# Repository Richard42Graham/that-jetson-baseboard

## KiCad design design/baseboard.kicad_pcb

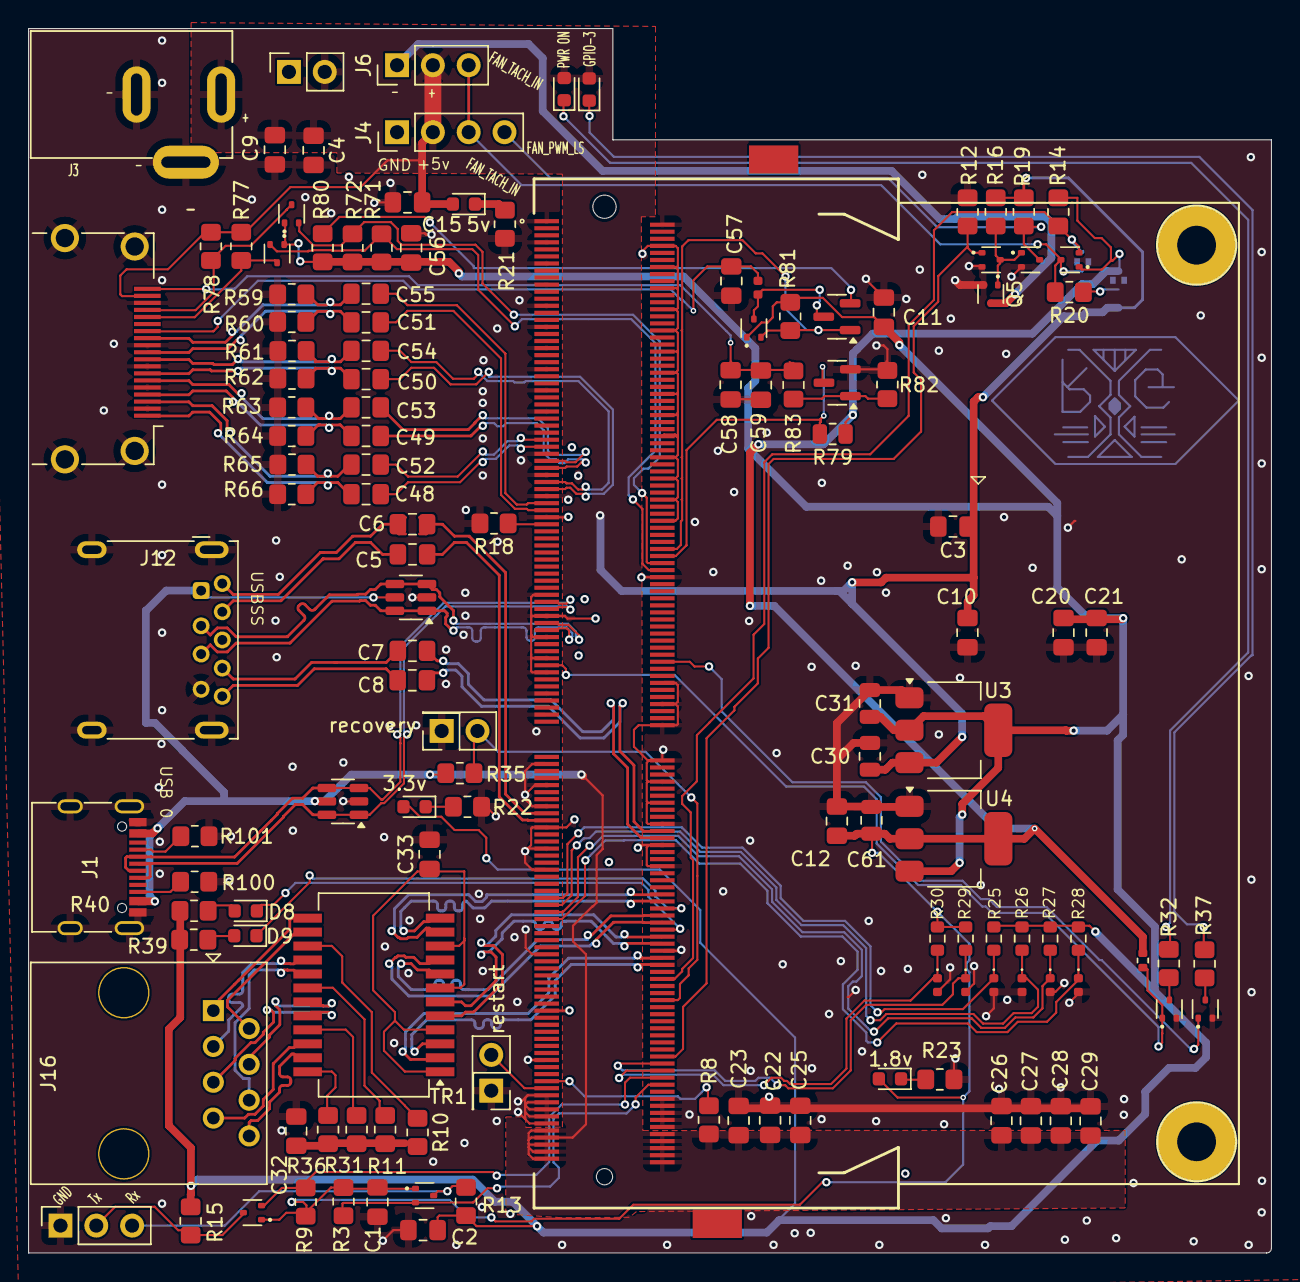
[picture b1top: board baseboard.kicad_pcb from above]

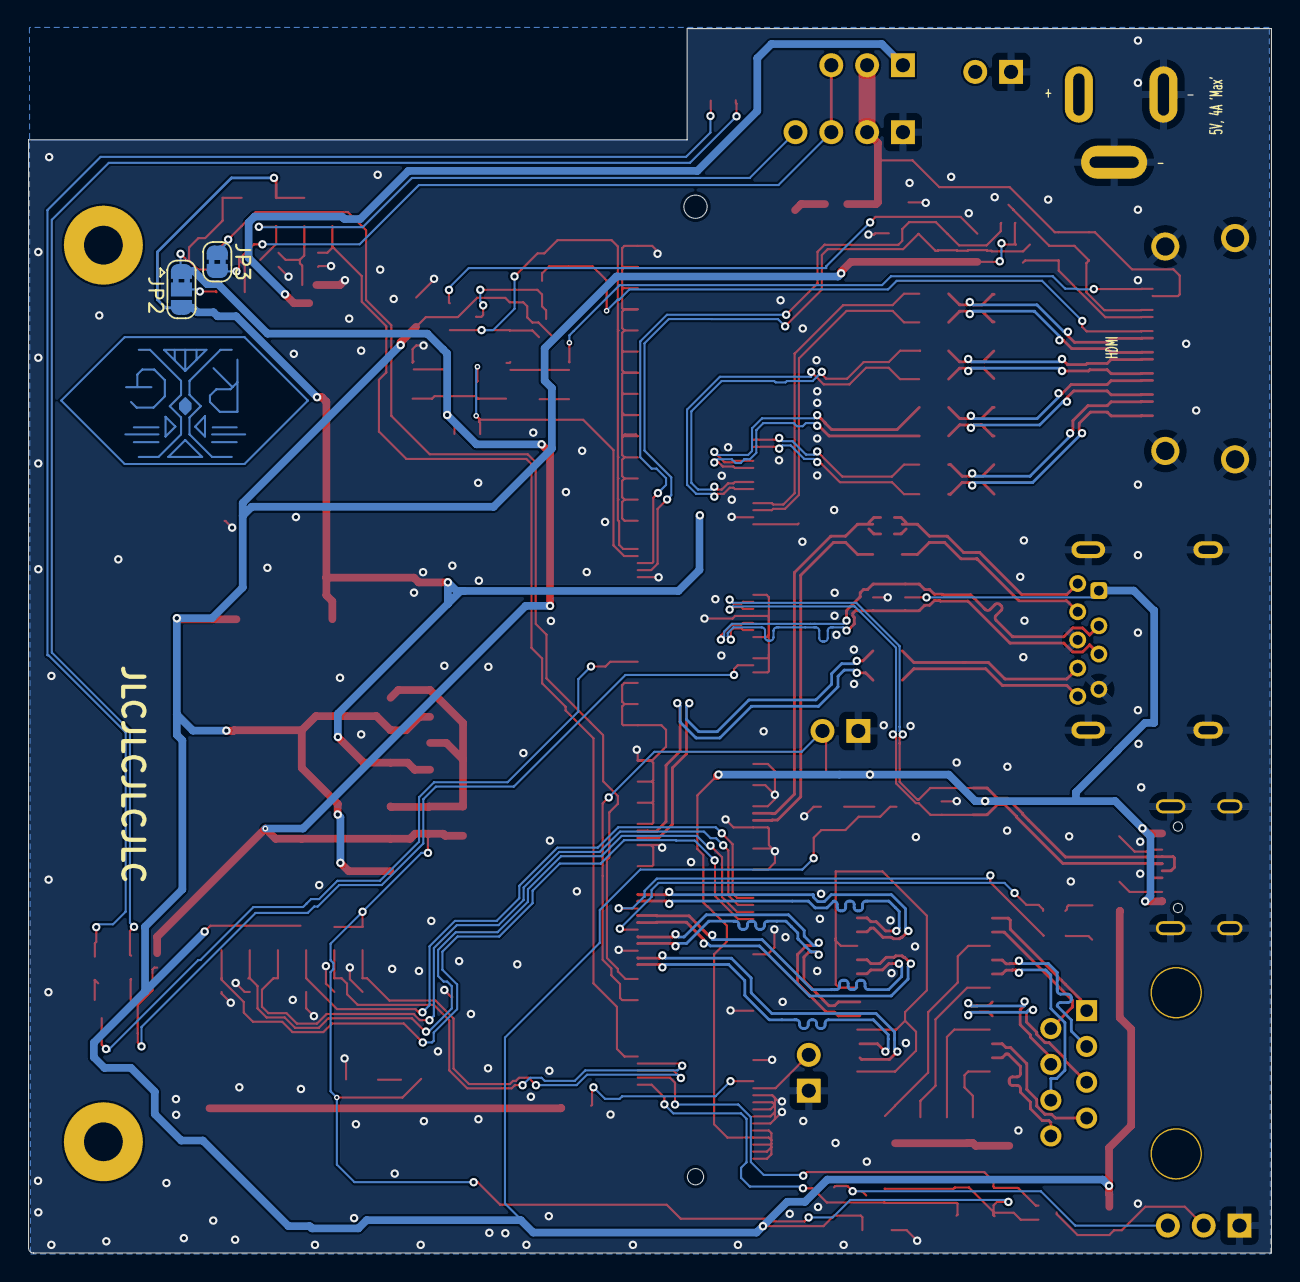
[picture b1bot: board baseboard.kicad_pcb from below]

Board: 2 copper layers, 88.2 x 86.9 mm, 134 parts (2 on the bottom side), 101 nets.

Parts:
C1, C2, C5, C6, C7, C8, C15, C48, C49, C50, C51, C52, C53, C54, C55, C56, C59: 0.1uF; C_0805_2012Metric_Pad1.18x1.45mm_HandSolder
C3, C4, C9, C22, C23, C25, C26, C27, C28, C29: 100uF; C_0805_2012Metric_Pad1.18x1.45mm_HandSolder
C10, C20: 10uF; C_0805_2012Metric_Pad1.18x1.45mm_HandSolder
C11, C12, C21: 1uF; C_0805_2012Metric_Pad1.18x1.45mm_HandSolder
C30, C31, C61: 10uF; C_0805_2012Metric
C32, C33: 100pF; C_0805_2012Metric_Pad1.18x1.45mm_HandSolder
C57, C58: 15pF; C_0805_2012Metric_Pad1.18x1.45mm_HandSolder
D1: 5v; LED_0603_1608Metric
D2, D20: USBLC6-2SC6; SOT-23-6
D3: 3.3v; LED_0603_1608Metric
D4: BAS70-05; SOT-23
D5: 1.8v; LED_0603_1608Metric
D6, D7: LED; LED_0603_1608Metric
D8: eth0; LED_0603_1608Metric
D9: eth1; LED_0603_1608Metric
D12, D13, D14, D15, D16, D17: TPD1E10B06DPYR; D_0402_1005Metric
J1: USB_C_Receptacle; USB_C_Receptacle_G-Switch_GT-USB-7010ASV
J2: Serial-2; PinSocket_1x03_P2.54mm_Vertical
J3: Jack-DC; NINIGI_DC-005
J4: Conn_01x04_Male; PinHeader_1x04_P2.54mm_Vertical
J5: 2309414-1; SODIMM-DDR4_8mm-NANO
J6: Conn_01x03_Pin; PinHeader_1x03_P2.54mm_Vertical
J8: power in; PinSocket_1x02_P2.54mm_Vertical
J10: restart; PinSocket_2x01_P2.54mm_Vertical
J11: HDMI_A; HDMI_A_Amphenol_10029449-111
J12: USB3_A; USB3_A_Molex_48393-001
J13: recovery; PinSocket_2x01_P2.54mm_Vertical
J16: RJ45; RJ45_OST_PJ012-8P8CX_Vertical
JP2: SolderJumper_3_Bridged12; SolderJumper-3_P1.3mm_Bridged2Bar12_RoundedPad1.0x1.5mm
JP3: SolderJumper_2_Bridged; SolderJumper-2_P1.3mm_Bridged2Bar_RoundedPad1.0x1.5mm
L2: 1.2nH; L_0402_1005Metric
Q1, Q2, Q3, Q4, Q5, Q6, Q7, Q11, Q12, Q13, Q14: DMN26D0UT-7; SOT-523
Q8: MMBT3904; SOT-23
R3, R8, R9, R12, R13, R14, R15, R19, R20, R35, R71, R72, R77, R78, R82, R83: 12k; R_0805_2012Metric_Pad1.20x1.40mm_HandSolder
R10, R11, R31, R36: 75r; R_0805_2012Metric_Pad1.20x1.40mm_HandSolder
R16, R18, R100, R101: 5.1k; R_0805_2012Metric_Pad1.20x1.40mm_HandSolder
R21, R22, R23, R32, R37, R39, R40: 220R; R_0805_2012Metric_Pad1.20x1.40mm_HandSolder
R25, R26, R27, R28, R29, R30: 2.2k; R_0603_1608Metric
R59, R60, R61, R62, R63, R64, R65, R66: 510r; R_0805_2012Metric_Pad1.20x1.40mm_HandSolder
R79: 12k; R_0805_2012Metric
R80: 36k; R_0805_2012Metric_Pad1.20x1.40mm_HandSolder
R81: 120k; R_0805_2012Metric_Pad1.20x1.40mm_HandSolder
R89: 12k; R_0402_1005Metric
TR1: G2415S; Transformer_Ethernet_HALO_TG111-MSC13
U3: AMS1117-3.3; SOT-223-3_TabPin2
U4: AMS1117-1.8; SOT-223-3_TabPin2

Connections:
+1V8: C1.1, C12.1, C61.1, D5.2 (A), JP2.1 (A), Q1.1 (G), Q2.1 (G), Q4.1 (G), R3.1, R9.1, R14.1, R29.1, R30.1, R79.1, R89.1, U4.2 (VO)
+3.3V: C2.1, C11.1, C20.1, C21.1, C31.1, C56.1, D3.2 (A), Q11.1 (G), Q13.1 (G), Q14.1 (G), R13.1, R15.1, R25.1, R26.1, R27.1, R28.1, R39.2, R40.1, R71.1, R72.1, R80.2, R81.1, U3.2 (VO), U4.3 (VI)
+5V: C3.1, C4.1, C9.1, C10.1, C15.1, C22.1, C23.1, C25.1, C26.1, C27.1, C28.1, C29.1, C30.1, D1.2 (A), D2.5 (VBUS), D6.2 (A), D7.2 (A), D20.5 (VBUS), J1.A4 (VBUS), J1.A9 (VBUS), J1.B4 (VBUS), J1.B9 (VBUS), J3.1, J4.2, J5.251 (VDD), J5.252 (VDD), J5.253 (VDD), J5.254 (VDD), J5.255 (VDD), J5.256 (VDD), J5.257 (VDD), J5.258 (VDD), J5.259 (VDD), J5.260 (VDD), J6.2, J8.2, J11.18 (+5V), J12.1 (VBUS), JP2.3 (B), R8.1, R16.1, R19.1, R35.1, R77.2, R78.2, U3.3 (VI)
/HDMI Connections Part 1/HDMI_DDC_SCL_POL_CON: J11.15 (SCL), Q11.3 (D), R77.1
/HDMI Connections Part 1/HDMI_DDC_SDA_POL_CON: J11.16 (SDA), Q13.3 (D), R78.1
/HDMI Connections Part 1/HDMI_TX0_CON_N: C54.1, J11.9 (D0-), R61.1
/HDMI Connections Part 1/HDMI_TX0_CON_P: C50.1, J11.7 (D0+), R62.1
/HDMI Connections Part 1/HDMI_TX1_CON_N: C53.1, J11.6 (D1-), R63.1
/HDMI Connections Part 1/HDMI_TX1_CON_P: C49.1, J11.4 (D1+), R64.1
/HDMI Connections Part 1/HDMI_TX2_CON_N: C52.1, J11.3 (D2-), R65.1
/HDMI Connections Part 1/HDMI_TX2_CON_P: C48.1, J11.1 (D2+), R66.1
/HDMI Connections Part 1/HDMI_TXC_CON_N: C55.1, J11.12 (CK-), R59.1
/HDMI Connections Part 1/HDMI_TXC_CON_P: C51.1, J11.10 (CK+), R60.1
/Power Regulation and Fan Tach/FAN_PWM_INV: Q3.1 (G), Q5.1 (G), Q12.3 (D), R16.2
/Power Regulation and Fan Tach/FAN_PWM_LS: J4.4, Q3.3 (D), R19.2
/Power Regulation and Fan Tach/FAN_TACH_IN: J4.3, J6.3, JP3.2 (B), Q4.3 (D), R20.2
/SODIMM Connections Part 2/VIS_LED_OUT: D7.1 (K), R37.1
/SODIMM Connections Part 2/VIS_SW_D: Q6.3 (D), R37.2
/SODIMM Connections Part 3/FORCE_RECOVERY*: J5.214 (~FORCE_RECOVERY), J13.2, R35.2
/UART to USB Bridge/C1_N: J16.2, TR1.14 (MX4+)
/UART to USB Bridge/C1_P: J16.1, TR1.13 (MX4-)
/UART to USB Bridge/C2_N: J16.6, TR1.17 (MX3+)
/UART to USB Bridge/C2_P: J16.3, TR1.16 (MX3-)
/UART to USB Bridge/C3_N: J16.5, TR1.20 (MX2+)
/UART to USB Bridge/C3_P: J16.4, TR1.19 (MX2-)
/UART to USB Bridge/C4_N: J16.8, TR1.23 (MX1+)
/UART to USB Bridge/C4_P: J16.7, TR1.22 (MX1-)
/USB2.0 Type A Hub/C_USBSS_RX1_N: C8.1, J12.5 (SSRX-)
/USB2.0 Type A Hub/C_USBSS_RX1_P: C7.1, J12.6 (SSRX+)
/USB2.0 Type A Hub/C_USBSS_TX1_N: C5.1, J12.8 (SSTX-)
/USB2.0 Type A Hub/C_USBSS_TX1_P: C6.1, J12.9 (SSTX+)
ENET_LED0: D8.1 (K), J5.194 (GBE_LED_ACT)
ENET_LED1: D9.1 (K), J5.188 (GBE_LED_LINK)
ENET_TRD0_N: J5.184 (GBE_MDI0_N), TR1.11 (TD4+)
ENET_TRD0_P: J5.186 (GBE_MDI0_P), TR1.12 (TD4-)
ENET_TRD1_N: J5.190 (GBE_MDI1_N), TR1.8 (TD3+)
ENET_TRD1_P: J5.192 (GBE_MDI1_P), TR1.9 (TD3-)
ENET_TRD2_N: J5.196 (GBE_MDI2_N), TR1.5 (TD2+)
ENET_TRD2_P: J5.198 (GBE_MDI2_P), TR1.6 (TD2-)
ENET_TRD3_N: J5.202 (GBE_MDI3_N), TR1.2 (TD1+)
ENET_TRD3_P: J5.204 (GBE_MDI3_P), TR1.3 (TD1-)
GND: C1.2, C2.2, C3.2, C4.2, C9.2, C10.2, C11.2, C12.2, C15.2, C20.2, C21.2, C22.2, C23.2, C25.2, C26.2, C27.2, C28.2, C29.2, C30.2, C31.2, C32.2, C33.2, C56.2, C57.2, C58.2, C59.2, C61.2, D2.2 (GND), D12.2 (A2), D13.2 (A2), D14.2 (A2), D15.2 (A2), D16.2 (A2), D17.2 (A2), D20.2 (GND), J1.A1 (GND), J1.A12 (GND), J1.B1 (GND), J1.B12 (GND), J1.S1 (SHIELD), J2.1, J3.2, J3.3, J4.1, J5.1 (GND), J5.2 (GND), J5.7 (GND), J5.8 (GND), J5.13 (GND), J5.14 (GND), J5.19 (GND), J5.20 (GND), J5.25 (GND), J5.26 (GND), J5.31 (GND), J5.32 (GND), J5.37 (GND), J5.38 (GND), J5.43 (GND), J5.44 (GND), J5.49 (GND), J5.50 (GND), J5.55 (GND), J5.56 (GND), J5.61 (GND), J5.62 (GND), J5.67 (GND), J5.68 (GND), J5.73 (GND), J5.74 (GND), J5.79 (GND), J5.80 (GND), J5.85 (GND), J5.86 (GND), J5.102 (GND), J5.107 (GND), J5.113 (GND), J5.119 (GND), J5.125 (GND), J5.129 (GND), J5.132 (GND), J5.135 (GND), J5.138 (GND), J5.141 (GND), J5.144 (GND), J5.146 (GND), J5.147 (GND), J5.152 (GND), J5.153 (GND), J5.158 (GND), J5.159 (GND), J5.164 (GND), J5.165 (GND), J5.170 (GND), J5.171 (GND), J5.176 (GND), J5.177 (GND), J5.200 (GND), J5.201 (GND), J5.217 (GND), J5.231 (GND), J5.241 (GND), J5.242 (GND), J5.243 (GND), J5.244 (GND), J5.245 (GND), J5.246 (GND), J5.247 (GND), J5.248 (GND), J5.249 (GND), J5.250 (GND), J8.1, J10.1, J11.2 (D2S), J11.5 (D1S), J11.8 (D0S), J11.11 (CKS), J11.17 (GND), J11.SH, J12.4 (GND), J12.7 (DRAIN), J12.10 (SHIELD), J13.1, Q3.2 (S), Q5.2 (S), Q6.2 (S), Q7.2 (S), Q8.2 (E), Q12.2 (S), R12.2, R18.2, R21.2, R22.2, R23.2, R59.2, R60.2, R61.2, R62.2, R63.2, R64.2, R65.2, R66.2, R82.2, R100.2, R101.2, U3.1 (GND), U4.1 (GND)
GPIO00: J5.87 (GPIO00_USB_VBUS_EN0), R18.1
GPIO03: J5.126 (GPIO03), Q6.1 (G)
GPIO04: J5.127 (GPIO04), Q7.1 (G), R89.2
GPIO08: J5.208 (GPIO08_SDMMC_CD), JP3.1 (A), Q4.2 (S), R14.2
GPIO14: J5.230 (GPIO14_PWM), Q12.1 (G), R12.1
HDMI_CEC: D4.1 (A1), J5.94 (HDMI_CEC), Q14.2 (S), R81.2
HDMI_CEC_CON: C57.1, J11.13 (CEC), L2.2
HDMI_DDC_SCL_POL: J5.100 (DP1_AUX_P), Q11.2 (S), R71.2
HDMI_DDC_SDA_POL: J5.98 (DP1_AUX_N), Q13.2 (S), R72.2
HDMI_HPD: J5.96 (DP1_HPD), Q8.3 (C), R79.2
HDMI_HPD_CON: C58.1, C59.1, J11.19 (HPD), R83.1
HDMI_TXC_N: C55.2, J5.81 (DP1_TXD3_N)
HDMI_TXC_P: C51.2, J5.83 (DP1_TXD3_P)
HDMI_TXD0_N: C54.2, J5.75 (DP1_TXD2_N)
HDMI_TXD0_P: C50.2, J5.77 (DP1_TXD2_P)
HDMI_TXD1_N: C53.2, J5.69 (DP1_TXD1_N)
HDMI_TXD1_P: C49.2, J5.71 (DP1_TXD1_P)
HDMI_TXD2_N: C52.2, J5.63 (DP1_TXD0_N)
HDMI_TXD2_P: C48.2, J5.65 (DP1_TXD0_P)
I2C0_SCL: D14.1 (A1), J5.185 (I2C0_SCL), R25.2
I2C0_SDA: D12.1 (A1), J5.187 (I2C0_SDA), R26.2
I2C1_SCL: D13.1 (A1), J5.189 (I2C1_SCL), R27.2
I2C1_SDA: D17.1 (A1), J5.191 (I2C1_SDA), R28.2
I2C2_SCL: D15.1 (A1), J5.232 (I2C2_SCL), R29.2
I2C2_SDA: D16.1 (A1), J5.234 (I2C2_SDA), R30.2
unnamed: C32.1, R10.2, R11.2, R31.2, R36.2
unnamed: D1.1 (K), R21.1
unnamed: D3.1 (K), R22.1
unnamed: D4.2 (A2), R80.1
unnamed: D4.3 (C), L2.1, Q14.3 (D)
unnamed: D5.1 (K), R23.1
unnamed: D6.1 (K), R32.1
unnamed: D8.2 (A), R40.2
unnamed: D9.2 (A), R39.1
unnamed: J1.A5 (CC1), R101.1
unnamed: J1.B5 (CC2), R100.1
unnamed: J2.2, Q2.3 (D), R15.2
unnamed: J2.3, Q1.3 (D), R13.2
unnamed: J6.1, Q5.3 (D)
unnamed: JP2.2 (C), R20.1
unnamed: Q7.3 (D), R32.2
unnamed: Q8.1 (B), R82.1, R83.2
unnamed: R36.1, TR1.24 (MCT1)
unnamed: R31.1, TR1.21 (MCT2)
unnamed: R11.1, TR1.18 (MCT3)
unnamed: R10.1, TR1.15 (MCT4)
unnamed: C33.1, TR1.1 (TCT1), TR1.4 (TCT2), TR1.7 (TCT3), TR1.10 (TCT4)
POWER_EN: J5.237 (POWER_EN), R8.2
SYS_RESET*: J5.239 (~SYS_RESET), J10.2
UART2_RXD: J5.238 (UART2_RXD_DEBUG), Q1.2 (S), R3.2
UART2_TXD: J5.236 (UART2_TXD_DEBUG), Q2.2 (S), R9.2
USB0_D_N: D2.3 (I/O2), D2.4 (I/O2), J1.A7 (D-), J1.B7 (D-), J5.109 (USB0_D_N)
USB0_D_P: D2.1 (I/O1), D2.6 (I/O1), J1.A6 (D+), J1.B6 (D+), J5.111 (USB0_D_P)
USB1_D_N: D20.3 (I/O2), D20.4 (I/O2), J5.115 (USB1_D_N), J12.2 (D-)
USB1_D_P: D20.1 (I/O1), D20.6 (I/O1), J5.117 (USB1_D_P), J12.3 (D+)
USBSS_RX6_N: C5.2, J5.163 (USBSS_RX_P)
USBSS_RX6_P: C6.2, J5.161 (USBSS_RX_N)
USBSS_TX6_N: C7.2, J5.168 (USBSS_TX_P)
USBSS_TX6_P: C8.2, J5.166 (USBSS_TX_N)

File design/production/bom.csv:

Designator,Footprint,Quantity,Value,LCSC Part #
"C1, C15, C2, C48, C49, C50, C51, C52, C53, C54, C55, C56, C59",0805,13,0.1uF,CL05B104KO5NNNC
"C10, C20, C30, C31, C61",0805,5,10uF,
"C11, C12",0805,2,1uF,CL05A105KA5NQNC
"C16, C17",0805,2,100pF,0402N101J500CT
C21,0805,1,1uF,
"C22, C23, C25, C26, C27, C28, C29, C3, C9",0805,9,100uF,T491B106M020AT
"C57, C58",0805,2,15pF,0402CG150J500NT
D1,0603,1,5v,XL-1608UGC-04
D2,SOT-23-6,1,USBLC6-2SC6,USBLC6-2SC6 
D3,0603,1,3.3v,XL-1608UGC-04
D4,SOT-23,1,BAS70-05,BAS70-05 
D5,0603,1,1.8v,XL-1608UGC-04
"D6, D7",0603,2,LED,XL-1608UGC-04 
D8,0603,1,eth0,XL-1608UGC-04
D9,0603,1,eth1,XL-1608UGC-04
J1,USB_C_Receptacle_G-Switch_GT-USB-7010ASV,1,USB_C_Receptacle,GT-USB-7010ASV 
J11,HDMI_A_Amphenol_10029449-111,1,HDMI_A,C427307
J12,USB3_A_Molex_48393-001,1,USB3_A,C3032863 USB Connectors USB 3.0 F/A STD CH 4.0 30u
J14,RJ45_OST_PJ012-8P8CX_Vertical,1,RJ45,C7205130
J5,SODIMM-DDR4_8mm-NANO,1,2309414-1,2309414-1
L2,0402,1,1.2nH,SDCL1005C1N2STDF
"Q1, Q11, Q12, Q13, Q14, Q2, Q3, Q4, Q6, Q7",SOT-523,10,DMN26D0UT-7,DMN26D0UT-7
Q8,SOT-23,1,MMBT3904,MMBT3904
"R100, R101, R16, R18",0805,4,5.1k,0402WGF5101TCE
"R12, R19, R82, R83",0805,4,12k,0402WGF1003TCE
"R13, R14, R15, R20, R3, R35, R71, R72, R79, R8, R9",0805,11,12k,0402WGF1002TCE
"R21, R22, R23, R32, R37",0805,5,220R,0603WAF1500T5E 
"R24, R33, R34, R38",0805,4,75r,
"R25, R26, R27, R28, R29, R30",0603,6,2.2k,0603WAF2201T5E
"R39, R40",0805,2,220R,ERJ2GEJ221X
"R59, R60, R61, R62, R63, R64, R65, R66",0805,8,510r,0402WGF5100TCE
"R77, R78",0805,2,12k,0603WAF1801T5E
R80,0805,1,36k,RTT03363JTP
R81,0805,1,120k,0402WGF1203TCE
TR3,Transformer_Ethernet_HALO_TG111-MSC13,1,G2415S,C3003219
U3,SOT-223-3_TabPin2,1,AMS1117-3.3,
U4,SOT-223-3_TabPin2,1,AMS1117-1.8,

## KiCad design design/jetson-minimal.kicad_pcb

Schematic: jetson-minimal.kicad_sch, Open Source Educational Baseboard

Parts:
C1, C2, C3, C8, C11: 1uF; C_0402_1005Metric; Tolerance 10%; MPN CL05A105KA5NQNC
C4: 100pF; C_0402_1005Metric; MPN 0402N101J500CT
C5: 4.7uF; C_0402_1005Metric; Tolerance 20%; MPN CL05A475MP5NRNC
C6: 0.1uF; C_0402_1005Metric; MPN CL05B104KO5NNNC
C7: 6.8pF; C_0402_1005Metric; Tolerance +/- 0.25pF; MPN 0402CG6R8C500NT
C9: 10uF; C_0603_1608Metric; Tolerance 20%; MPN CL10A106MA8NRNC
C10: 10uF; C_0603_1608Metric; Tolerance 20%; not fitted
C12, C13: 100uF; CP_EIA-3528-12_Kemet-T; Tolerance 20%; MPN RVT1E101M0607
C14: 330uF; C_Elec_6.3x7.7; Tolerance 20%; MPN TAJD337K010RNJ
C15: 0.1uF; C_0402_1005Metric; Tolerance 10%; MPN CL05B104KO5NNNC
C16, C17, C18, C19, C20, C21, C22, C23: 10uF; C_0805_2012Metric_Pad1.18x1.45mm_HandSolder; Tolerance 20%; MPN CL10A106MA8NRNC
D1: RB521S30T1G; SOD-523; MPN RB521S30T1G
D2, D3: LED; LED_0603_1608Metric; MPN BL-HUF36D-AV-TRB
D4: USBLC6-2SC6; SOT-23-6; MPN USBLC6-2SC6
H1, H2, H3, H4: MountingHole_Pad; MountingHole_3.2mm_M3_Pad_Via; not fitted
J1: SI-51005-F; MPN SI-51005-F; not fitted
J2: RJ45_RB1-125B8G1A; RJ45_UDE_RB1-125B8G1A; MPN RB1-125B8G1A
J3: Jack-DC; NINIGI_DC-005
J4: power in; PinSocket_1x02_P2.54mm_Vertical; not fitted
J5: 2309414-1; SODIMM-DDR4_8mm-NANO; MPN 2309414-1
J6: Conn_01x04_Male; PinHeader_1x04_P2.54mm_Vertical
J7: USB_C_Receptacle; USB_C_Receptacle_G-Switch_GT-USB-7010ASV; MPN 1054500101
J8: PROG; PinSocket_1x02_P2.54mm_Vertical
J9: reset; PinSocket_1x02_P2.54mm_Vertical
JP1: SolderJumper_2_Open; SolderJumper-2_P1.3mm_Open_TrianglePad1.0x1.5mm; not fitted
L1: 2.2uH; L_Bourns_SRP7028A_7.3x6.6mm; MPN YSPI0730-2R2M
Q1, Q2, Q3, Q4, Q5, Q6: DMN26D0UT-7; SOT-523; MPN DMN26D0UT-7
R1, R6, R10: 100k; R_0603_1608Metric_Pad0.98x0.95mm_HandSolder; MPN 0402WGF1003TCE
R2, R3: 220R; R_0402_1005Metric; MPN ERJ2GEJ221X; not fitted
R4, R5: 220R; R_0603_1608Metric_Pad0.98x0.95mm_HandSolder; MPN 0402WGF2200TCE
R7, R30, R31: 5.1k; R_0603_1608Metric_Pad0.98x0.95mm_HandSolder; MPN 0402WGF5101TCE
R8: 470K; R_0603_1608Metric_Pad0.98x0.95mm_HandSolder; Tolerance 5%; MPN 0805W8F4703T5E
R9: 120k; R_0603_1608Metric_Pad0.98x0.95mm_HandSolder; Tolerance 1%; MPN 0402WGF1203TCE
R11, R12, R21: 12k; R_0603_1608Metric_Pad0.98x0.95mm_HandSolder; MPN 0805W8F1202T5E
R13, R29, R34: 12k; R_0603_1608Metric_Pad0.98x0.95mm_HandSolder; Tolerance 5%; MPN 0805W8F1202T5E
R14: 100R; R_0603_1608Metric_Pad0.98x0.95mm_HandSolder; Tolerance 1%; MPN 0402WGF1000TCE
R15, R18, R32, R33: 0; R_0603_1608Metric_Pad0.98x0.95mm_HandSolder; Tolerance 5%; MPN 0402WGF0000TCE
R16: 4.7k; R_0603_1608Metric_Pad0.98x0.95mm_HandSolder; Tolerance 1%; MPN 0402WGF4701TCE
R17: 150r; R_0603_1608Metric_Pad0.98x0.95mm_HandSolder; Tolerance 1%; MPN 0603WAF1500T5E
R19: 1k; R_0603_1608Metric_Pad0.98x0.95mm_HandSolder; Tolerance 1%; MPN 0402WGF1001TCE
R20: 12k; R_0603_1608Metric_Pad0.98x0.95mm_HandSolder; Tolerance 1%; MPN 0805W8F1202T5E
R22: 150r; R_0603_1608Metric; Tolerance 1%; MPN 0603WAF1500T5E
R23, R24: 2.2k; R_0603_1608Metric; Tolerance 5%; MPN 0603WAF2201T5E
R25, R26, R27, R28: 2.2k; R_0603_1608Metric; MPN 0603WAF2201T5E
R35: 100k; R_0603_1608Metric_Pad0.98x0.95mm_HandSolder; Tolerance 5%; MPN 0402WGF1004TCE
R36, R37: ??; R_0603_1608Metric_Pad0.98x0.95mm_HandSolder; Tolerance 1%; MPN 0402WGF1000TCE; not fitted
TP1, TP2: TestPoint; TestPoint_Pad_D2.0mm; not fitted
U1, U4: 74LVC1G126; SOT-353_SC-70-5; MPN 74LVC1G126GW,125
U2: TLV62569DDC; SOT-23-6; MPN TLV62569DBVR
U3: TLV70018DCKT; SOT-353_SC-70-5; MPN TLV70018DCKT
U5: CONV_AL8861Y-13; not fitted

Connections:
3V3_PGOOD: R20.2, U2.5 (PG), U3.3 (EN)
+1V8: C11.1, Q5.1 (G), R11.1, R13.1, R21.1, R27.1, R28.1, U3.5 (OUT)
+3.3V: C8.1, C9.1, C10.1, C23.1, L1.2, R2.2, R3.1, R4.2, R5.1, R9.1, R14.1, R20.1, R23.1, R24.1, R25.1, R26.1, R36.1, U3.1 (IN), U5.5 (out)
+5V: C1.1, C3.1, C5.1, C6.1, C12.1, C13.1, C14.1, C16.1, C17.1, C18.1, C19.1, C20.1, C21.1, C22.1, D2.2 (A), D3.2 (A), D4.5 (VBUS), J3.1, J4.2, J5.251 (VDD), J5.252 (VDD), J5.253 (VDD), J5.254 (VDD), J5.255 (VDD), J5.256 (VDD), J5.257 (VDD), J5.258 (VDD), J5.259 (VDD), J5.260 (VDD), J6.2, JP1.2 (B), R7.1, R10.1, R12.1, R29.1, R34.1, U1.1, U1.5 (VCC), U2.4 (VIN), U4.1, U4.5 (VCC), U5.4 (Vin)
/3V3BUCK_CAP_IN: C7.1, R14.2, R16.1
/3V3BUCK_FB: C7.2, R16.2, R19.1, U2.6 (FB)
/3V3BUCK_SW: L1.1, U2.3 (SW)
/FAN_PWM_INV: Q3.3 (D), Q4.1 (G), R7.2
/FAN_PWM_LS: J6.4, Q4.3 (D), R10.2
/FAN_TACH_IN: J6.3, Q5.3 (D), R12.2
/FORCE_RECOVERY*: J5.214 (~FORCE_RECOVERY), J8.2, R29.2
/USB0_FILT_N: D4.3 (I/O2), D4.4 (I/O2), J7.A7 (D-), J7.B7 (D-), R33.1
/USB0_FILT_P: D4.1 (I/O1), D4.6 (I/O1), J7.A6 (D+), J7.B6 (D+), R32.2
/VBUS_USB0: C15.1, J7.A4 (VBUS), J7.A9 (VBUS), J7.B4 (VBUS), J7.B9 (VBUS), JP1.1 (A), Q6.1 (G), R35.1
/VIS_LED_OUT: D2.1 (K), R17.1
/VIS_SW_D: Q1.3 (D), R17.2
/VIS_SW_G: Q1.1 (G), R15.2
EGND: C4.1, J1.S (SHIELD), J2.SH
ENET_LED0: J1.13, J2.L4, J5.194 (GBE_LED_ACT)
ENET_LED1: J1.11, J2.L2, J5.188 (GBE_LED_LINK)
ENET_TRD0_N: J1.3 (D0-), J2.R3 (TD1-), J5.184 (GBE_MDI0_N)
ENET_TRD0_P: J1.2 (D0+), J2.R2 (TD1+), J5.186 (GBE_MDI0_P)
ENET_TRD1_N: J1.5 (D1-), J2.R5 (TD2-), J5.190 (GBE_MDI1_N)
ENET_TRD1_P: J1.4 (D1+), J2.R4 (TD2+), J5.192 (GBE_MDI1_P)
ENET_TRD2_N: J1.8 (D2-), J2.R6 (TD3+), J5.196 (GBE_MDI2_N)
ENET_TRD2_P: J1.7 (D2+), J2.R7 (TD3-), J5.198 (GBE_MDI2_P)
ENET_TRD3_N: J1.10 (D3-), J2.R8 (TD4+), J5.202 (GBE_MDI3_N)
ENET_TRD3_P: J1.9 (D3+), J2.R9 (TD4-), J5.204 (GBE_MDI3_P)
GND: C1.2, C2.2, C3.2, C4.2, C5.2, C6.2, C8.2, C9.2, C10.2, C11.2, C12.2, C13.2, C14.2, C15.2, C16.2, C17.2, C18.2, C19.2, C20.2, C21.2, C22.2, C23.2, D4.2 (GND), H1.1, H2.1, H3.1, H4.1, J1.1 (GND), J2.R10 (GND), J3.2, J3.3, J4.1, J5.1 (GND), J5.2 (GND), J5.7 (GND), J5.8 (GND), J5.13 (GND), J5.14 (GND), J5.19 (GND), J5.20 (GND), J5.25 (GND), J5.26 (GND), J5.31 (GND), J5.32 (GND), J5.37 (GND), J5.38 (GND), J5.43 (GND), J5.44 (GND), J5.49 (GND), J5.50 (GND), J5.55 (GND), J5.56 (GND), J5.61 (GND), J5.62 (GND), J5.67 (GND), J5.68 (GND), J5.73 (GND), J5.74 (GND), J5.79 (GND), J5.80 (GND), J5.85 (GND), J5.86 (GND), J5.102 (GND), J5.107 (GND), J5.113 (GND), J5.119 (GND), J5.125 (GND), J5.129 (GND), J5.132 (GND), J5.135 (GND), J5.138 (GND), J5.141 (GND), J5.144 (GND), J5.146 (GND), J5.147 (GND), J5.152 (GND), J5.153 (GND), J5.158 (GND), J5.159 (GND), J5.164 (GND), J5.165 (GND), J5.170 (GND), J5.171 (GND), J5.176 (GND), J5.177 (GND), J5.200 (GND), J5.201 (GND), J5.217 (GND), J5.231 (GND), J5.241 (GND), J5.242 (GND), J5.243 (GND), J5.244 (GND), J5.245 (GND), J5.246 (GND), J5.247 (GND), J5.248 (GND), J5.249 (GND), J5.250 (GND), J6.1, J7.A1 (GND), J7.A12 (GND), J7.B1 (GND), J7.B12 (GND), J7.S1 (SHIELD), J8.1, J9.1, Q1.2 (S), Q2.2 (S), Q3.2 (S), Q4.2 (S), Q6.2 (S), R1.2, R6.2, R19.2, R30.2, R31.2, R35.2, R37.2, U1.3 (GND), U2.2 (GND), U3.2 (GND), U4.3 (GND), U5.2 (GND)
GPIO00: J5.87 (GPIO00_USB_VBUS_EN0), Q6.3 (D)
GPIO01: J5.118 (GPIO01_CLK)
GPIO02: J5.124 (GPIO02)
GPIO03: J5.126 (GPIO03), R15.1
GPIO04: J5.127 (GPIO04), R18.1
GPIO05: J5.128 (GPIO05)
GPIO06: J5.130 (GPIO06)
GPIO07: J5.206 (GPIO07_PWM), R1.1
GPIO08: J5.208 (GPIO08_SDMMC_CD), Q5.2 (S), R11.2
GPIO09: J5.211 (GPIO09_AUD_MCLK)
GPIO10: J5.212 (GPIO10)
GPIO11: J5.216 (GPIO11_CLK)
GPIO12: J5.218 (GPIO12)
GPIO13: J5.228 (GPIO13_PWM)
GPIO14: J5.230 (GPIO14_PWM), Q3.1 (G), R6.1
HDMI_CEC: J5.94 (HDMI_CEC), R9.2
HDMI_DDC_SCL_POL: J5.100 (DP1_AUX_P)
HDMI_DDC_SDA_POL: J5.98 (DP1_AUX_N)
HDMI_HPD: J5.96 (DP1_HPD), R13.2
HDMI_TXC_N: J5.81 (DP1_TXD3_N)
HDMI_TXC_P: J5.83 (DP1_TXD3_P)
HDMI_TXD0_N: J5.75 (DP1_TXD2_N)
HDMI_TXD0_P: J5.77 (DP1_TXD2_P)
HDMI_TXD1_N: J5.69 (DP1_TXD1_N)
HDMI_TXD1_P: J5.71 (DP1_TXD1_P)
HDMI_TXD2_N: J5.63 (DP1_TXD0_N)
HDMI_TXD2_P: J5.65 (DP1_TXD0_P)
I2C0_SCL: J5.185 (I2C0_SCL), R23.2
I2C0_SDA: J5.187 (I2C0_SDA), R24.2
I2C1_SCL: J5.189 (I2C1_SCL), R25.2
I2C1_SDA: J5.191 (I2C1_SDA), R26.2
I2C2_SCL: J5.232 (I2C2_SCL), R27.2
I2C2_SDA: J5.234 (I2C2_SDA), R28.2
I2S0_LRCK: J5.197 (I2S0_FS)
I2S0_SCLK: J5.199 (I2S0_SCLK)
I2S0_SDIN: J5.195 (I2S0_DIN)
I2S0_SDOUT: J5.193 (I2S0_DOUT)
MOD_SLEEP*: J5.178 (~MOD_SLEEP)
unnamed: C2.1, D1.2 (A), R8.2, U4.2
unnamed: D1.1 (K), R8.1, U1.4
unnamed: D3.1 (K), R22.1
unnamed: J1.12, R2.1
unnamed: J1.14, R3.2
unnamed: J2.L1, R5.2
unnamed: J2.L3, R4.1
unnamed: J7.A5 (CC1), R31.1
unnamed: J7.B5 (CC2), R30.1
unnamed: Q2.3 (D), R22.2
unnamed: Q2.1 (G), R18.2, R21.2
unnamed: R36.2, R37.1, U5.3 (ADJ)
POWER_EN: J5.237 (POWER_EN), TP2.1, U4.4
SHUTDOWN_REQ*: J5.233 (~SHUTDOWN_REQ), TP1.1, U1.2
SLEEP_WAKE*: J5.240 (~SLEEP_WAKE)
SPI0_CS0: J5.95 (SPI0_CS0)
SPI0_CS1: J5.97 (SPI0_CS1)
SPI0_MISO: J5.93 (SPI0_MISO)
SPI0_MOSI: J5.89 (SPI0_MOSI)
SPI0_SCK: J5.91 (SPI0_SCK)
SPI1_CS0: J5.110 (SPI1_CS0)
SPI1_CS1: J5.112 (SPI1_CS1)
SPI1_MISO: J5.108 (SPI1_MISO)
SPI1_MOSI: J5.104 (SPI1_MOSI)
SPI1_SCK: J5.106 (SPI1_SCK)
SYS_RESET*: J5.239 (~SYS_RESET), J9.2, R34.2, U2.1 (EN), U5.1 (EN)
UART1_CTS: J5.209 (UART1_CTS)
UART1_RTS: J5.207 (UART1_RTS)
UART1_RXD: J5.205 (UART1_RXD)
UART1_TXD: J5.203 (UART1_TXD)
UART2_RXD: J5.238 (UART2_RXD_DEBUG)
UART2_TXD: J5.236 (UART2_TXD_DEBUG)
USB0_D_N: J5.109 (USB0_D_N), R33.2
USB0_D_P: J5.111 (USB0_D_P), R32.1
USB1_D_N: J5.115 (USB1_D_N)
USB1_D_P: J5.117 (USB1_D_P)
USBSS_RX6_N: J5.163 (USBSS_RX_P)
USBSS_RX6_P: J5.161 (USBSS_RX_N)
USBSS_TX6_N: J5.168 (USBSS_TX_P)
USBSS_TX6_P: J5.166 (USBSS_TX_N)

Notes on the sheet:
RLC values chosen based on TI WBENCH calculator, then scaled to remain <100k. Parameters: 5V-3V3, 2A output
Vfb
Note: for more robustness, additional power protection (over/under voltage or current, slew rate, etc) can be added. It is assumed that the hobbyist user will choose an appropriate power supply for their board.
All 0603, 5%, COMMON
max says have a mosfet controling this output, to prevent laod on the jetson pin.
max
no stuff this capacitor
Fan Tach Signals
SODIMM CONNECTIONS PART 2
no stuff these pullups
SODIMM CONNECTIONS PART 3
Output Voltage with Tolerance
No stuff the common mode choke, co-locate resistors to avoid stubs
no stuff option for debouncing
Vout
1V8 LDO
POWER AND FAN TACH
ADD 5v power to VBUS control from GPIO, ask MAX
Power Indicator LED
3.42V
0.612V
consider replacing with a usb c port for niceness.
POWER ON/OFF LOGIC
SODIMM CONNECTIONS PART 1
Visual Feedback LED
All capacitors rated 6.3V, X5R, COMMON, 10%, 0402 All resistors have tolerance 5%, 0402, COMMON Except where noted
PLUG 5.5mm OD, 2.0mm ID
5V Power Protection
3.3516V
0.588V
DEBUG MICRO USB CONNECTIONS
3V3 AND 1V8 POWER SUPPLY
min
0.6V
Max says no place!
nom
5V to 3V3 Buck Converter
3.4884V

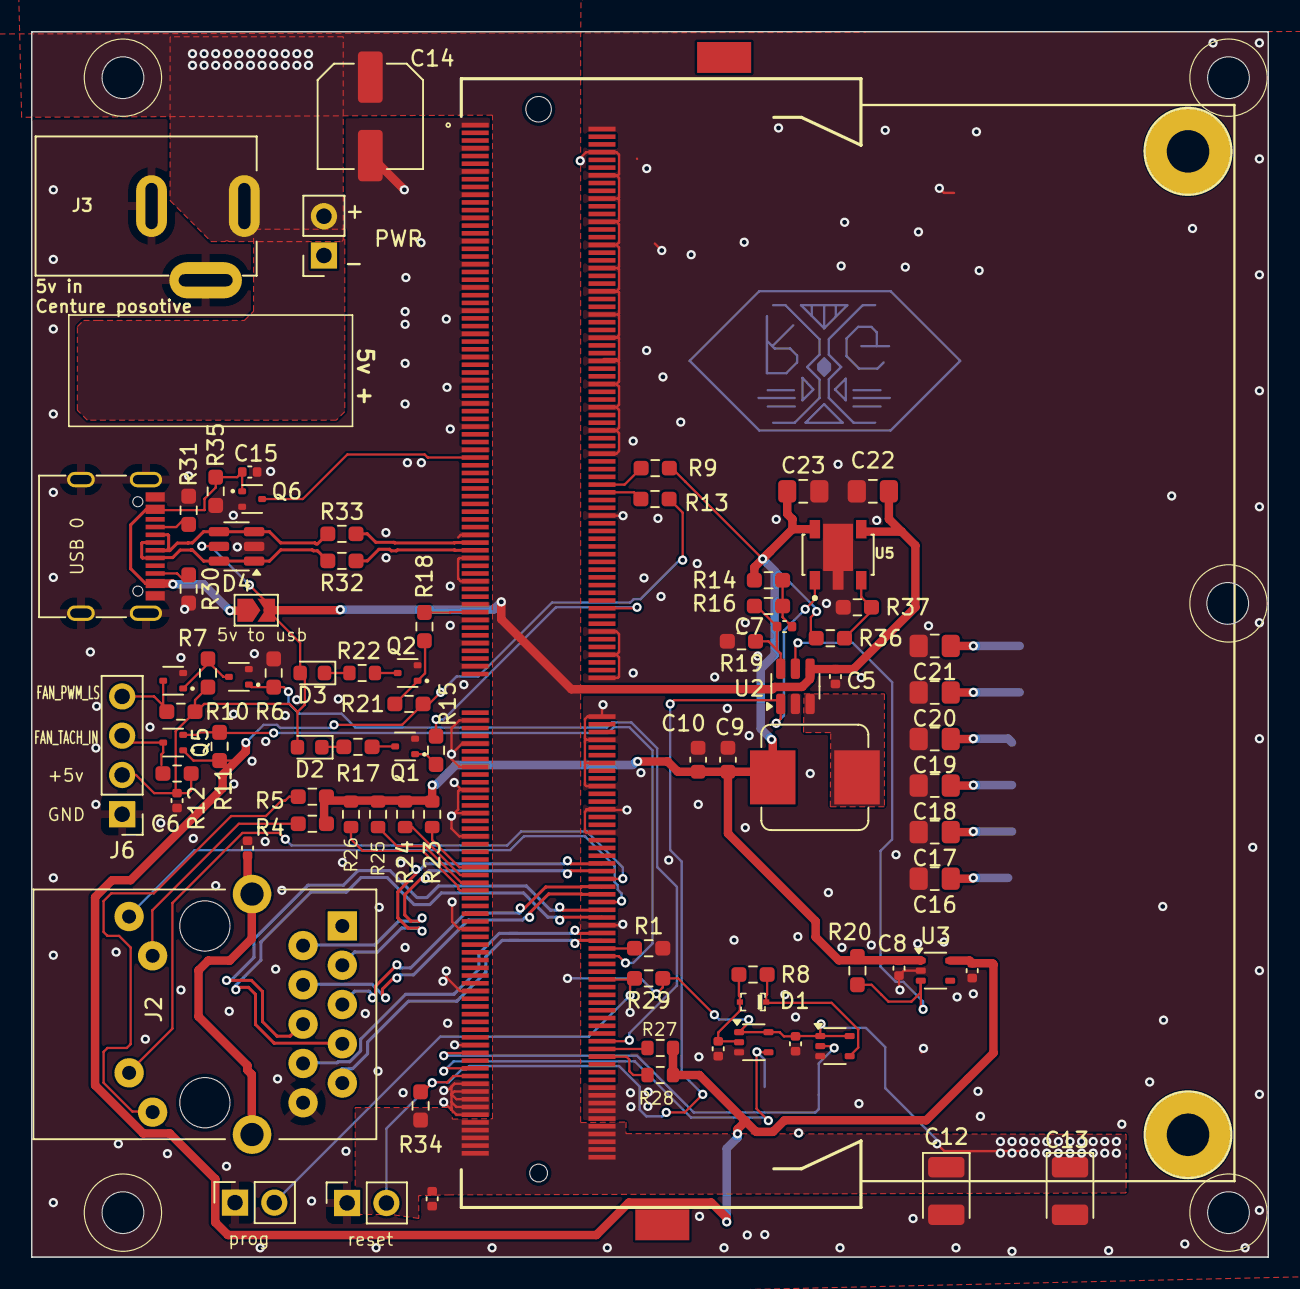
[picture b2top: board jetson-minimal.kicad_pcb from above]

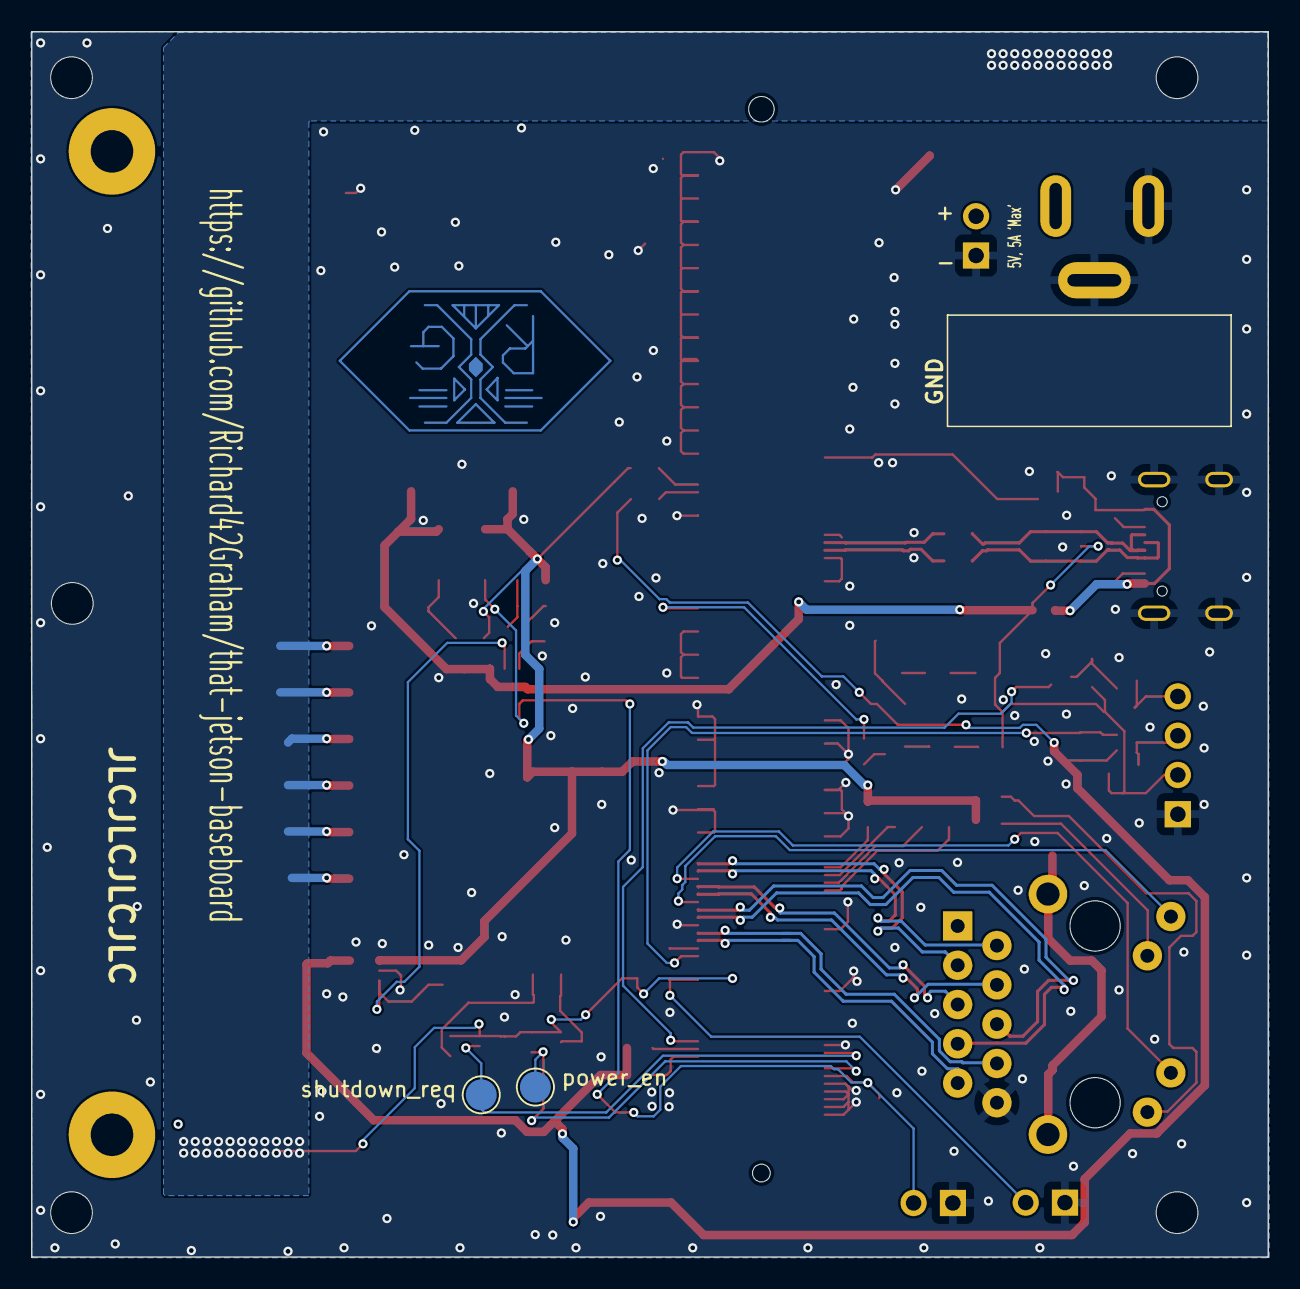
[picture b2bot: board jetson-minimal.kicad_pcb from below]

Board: 2 copper layers, 80.0 x 79.2 mm, 85 parts (2 on the bottom side), 58 nets.

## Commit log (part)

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2025-06-11 removed most components, and re did layout
2025-06-11 updaed some compoent footprints and layouts to make it easier for manufacturing
2025-06-11 refinemnet
2025-06-15 produced production files for PCB fabrication.
2025-06-15 updated the actual files.
2025-07-10 updated 3d modles for jetson holder, and usb c port, and updated the part numbers as well
